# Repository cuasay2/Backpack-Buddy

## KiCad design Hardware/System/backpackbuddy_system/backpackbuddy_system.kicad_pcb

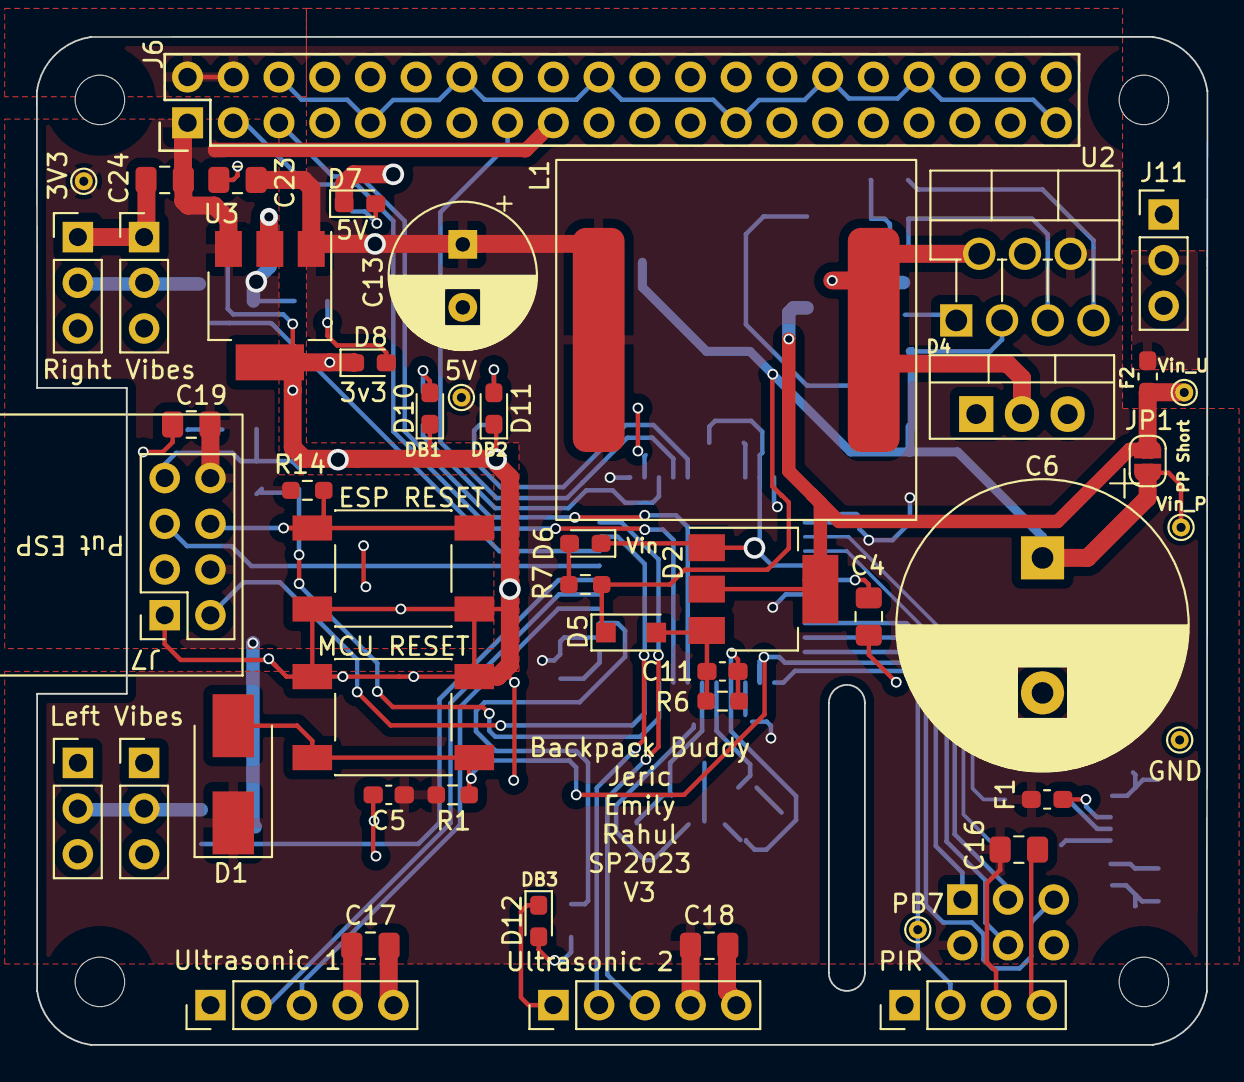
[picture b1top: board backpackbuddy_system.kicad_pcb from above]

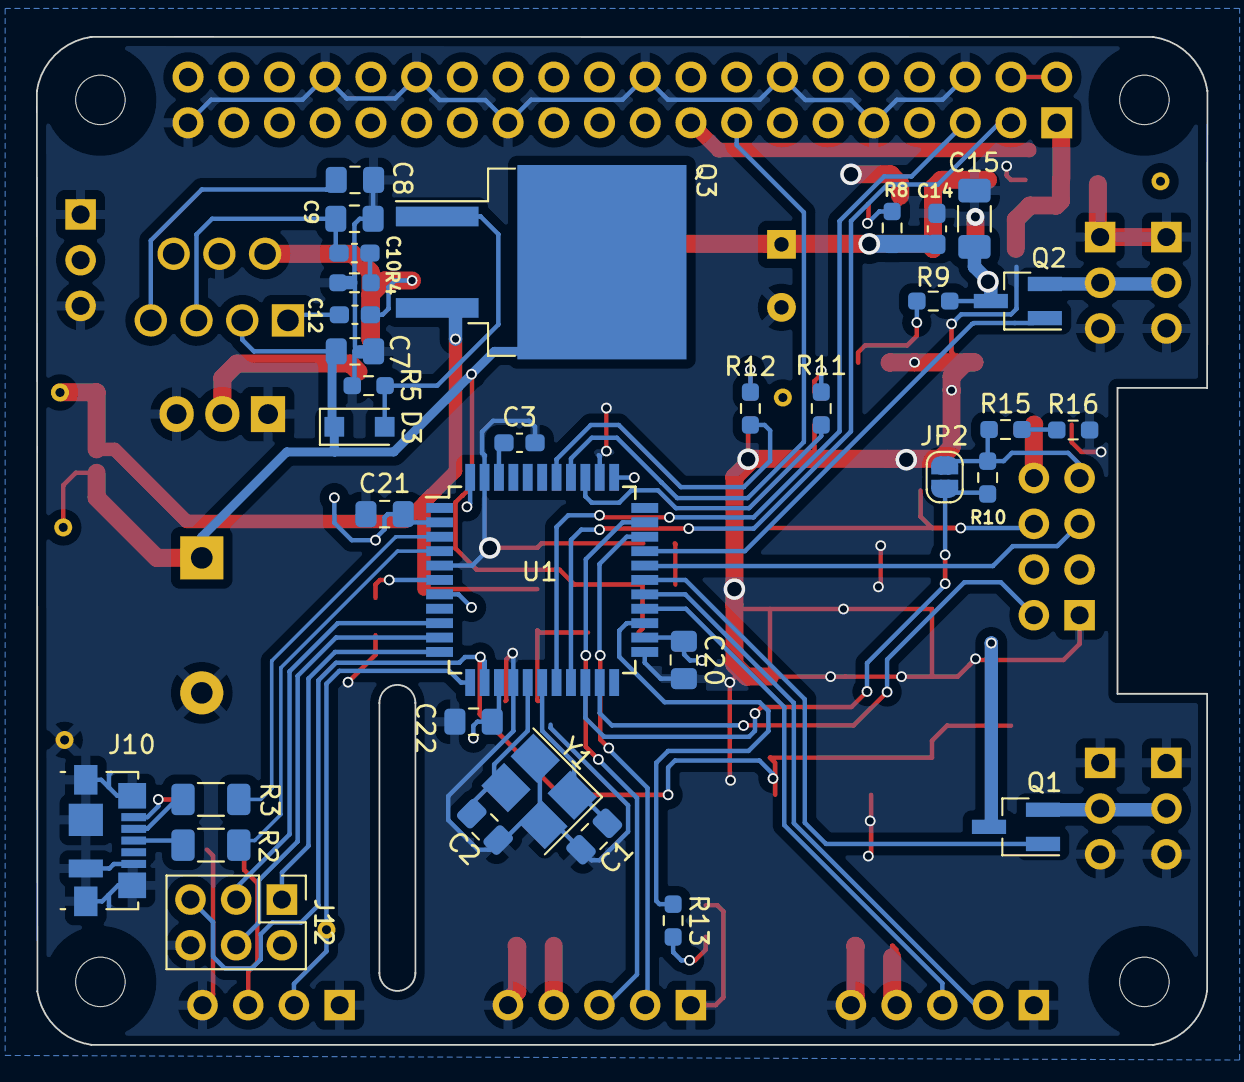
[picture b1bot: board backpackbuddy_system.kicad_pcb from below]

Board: 2 copper layers, 65.0 x 56.0 mm, 87 parts (34 on the bottom side), 53 nets.

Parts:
C1, C2: 22pF; C_0805_2012Metric_Pad1.18x1.45mm_HandSolder
C3, C5, C11: 0.1uF; C_0603_1608Metric_Pad1.08x0.95mm_HandSolder
C4: 1uF; C_0805_2012Metric_Pad1.18x1.45mm_HandSolder
C6: 2200uF; CP_Radial_D16.0mm_P7.50mm
C7: 4.7uF; C_0805_2012Metric_Pad1.18x1.45mm_HandSolder
C8, C16, C17, C18, C19, C20, C21, C22, C23, C24: 10uF; C_0805_2012Metric_Pad1.18x1.45mm_HandSolder
C9: 680pF; C_0805_2012Metric_Pad1.18x1.45mm_HandSolder
C10: 1200pF; C_0603_1608Metric_Pad1.08x0.95mm_HandSolder
C12: 0.22uF; C_0603_1608Metric_Pad1.08x0.95mm_HandSolder
C13: 470uF; CP_Radial_D8.0mm_P3.50mm
C14: 0.47uF; C_0603_1608Metric_Pad1.08x0.95mm_HandSolder
C15: 33uF; C_1206_3216Metric_Pad1.33x1.80mm_HandSolder
D1: 1V; D_SMB_Handsoldering
D2: S602TS; SOT-223-3_TabPin2
D3: 20V; D_SOD-123F
D4: FMW-2156; TO-220-3_Vertical
D5: 27V; D_SOD-123F
D6: Vin; LED_0603_1608Metric_Pad1.05x0.95mm_HandSolder
D7: 5V; LED_0603_1608Metric_Pad1.05x0.95mm_HandSolder
D8: 3v3; LED_0603_1608Metric_Pad1.05x0.95mm_HandSolder
D10: DB1; LED_0603_1608Metric_Pad1.05x0.95mm_HandSolder
D11: DB2; LED_0603_1608Metric_Pad1.05x0.95mm_HandSolder
D12: DB3; LED_0603_1608Metric_Pad1.05x0.95mm_HandSolder
F1: 500mA; Fuse_0603_1608Metric_Pad1.05x0.95mm_HandSolder
F2: 4A; Fuse_0603_1608Metric_Pad1.05x0.95mm_HandSolder
H1, H2, H3, H4: MountingHole; RPi_Hat_Mounting_Hole
J1: PIR; PinHeader_1x04_P2.54mm_Vertical
J2: Ultrasonic 2; PinHeader_1x05_P2.54mm_Vertical
J3: Ultrasonic 1; PinHeader_1x05_P2.54mm_Vertical
J4: Left Vibes; PinHeader_1x03_P2.54mm_Vertical
J5: Left Vibration 2; PinHeader_1x03_P2.54mm_Vertical
J6: RPi_GPIO; Pin_Header_Straight_2x20
J7: ESP8266
J8: Right Vibes; PinHeader_1x03_P2.54mm_Vertical
J9: Right Vibration 2; PinHeader_1x03_P2.54mm_Vertical
J10: USB_B_Micro; USB_Micro-B_Molex_47346-0001
J11: Battery; PinHeader_1x03_P2.54mm_Vertical
J12: ICSP; PinHeader_2x03_P2.54mm_Vertical
JP1, JP2: PP Short; SolderJumper-2_P1.3mm_Open_RoundedPad1.0x1.5mm
L1: 56uH; Inductor_IHLP6767GZER560M11
PB7: PIR; TestPoint_THTPad_D1.0mm_Drill0.5mm
Q1, Q2: Q_NMOS_GSD; SOT-23_Handsoldering
Q3: SIHF9Z24STRR-GE3; TO-263-2
R1, R7, R14: 10k; R_0603_1608Metric_Pad0.98x0.95mm_HandSolder
R2, R3: 22; R_1206_3216Metric_Pad1.30x1.75mm_HandSolder
R4: 39k; R_0603_1608Metric_Pad0.98x0.95mm_HandSolder
R5, R6, R8, R9, R10, R11, R12, R13, R15, R16: 1k; R_0603_1608Metric_Pad0.98x0.95mm_HandSolder
SW1: ESP RESET; RST_SW
SW2: MCU RESET; RST_SW
TP1: Vin_U; TestPoint_THTPad_D1.0mm_Drill0.5mm
TP2: GND; TestPoint_THTPad_D1.0mm_Drill0.5mm
TP3: Vin_P; TestPoint_THTPad_D1.0mm_Drill0.5mm
TP4: 5V; TestPoint_THTPad_D1.0mm_Drill0.5mm
TP5: 3V3; TestPoint_THTPad_D1.0mm_Drill0.5mm
U1: ATmega32U4-A; TQFP-44_10x10mm_P0.8mm
U2: SI-8050Y; TO-220F-7_P2.54x3.7mm_StaggerOdd_Lead3.5mm_Vertical
U3: LM3940; SOT-223
Y1: 16MHz; Crystal_SMD_3225-4Pin_3.2x2.5mm_HandSoldering

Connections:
+3V3: C15.1, C19.1, C24.1, J6.1, J6.17, J7.4, J7.8, Q1.3 (D), Q2.3 (D), R9.1, R14.1, TP5.1, U3.3 (Vout)
+5V: C5.1, C13.1, C14.1, C16.1, C17.1, C18.1, C20.1, C21.1, C22.1, C23.1, D1.1 (K), F1.2, J1.3, J2.4, J3.4, J6.2, J6.4, J12.2, L1.2, R1.1, R8.1, TP4.1, U1.2 (UVCC), U1.7 (VBUS), U1.14 (VCC), U1.24 (AVCC), U1.34 (VCC), U1.44 (AVCC), U2.6 (FB), U3.1 (Vin)
/ESP RESET: J7.6, R14.2, SW1.1
/ESP_RX: J7.7, JP2.1 (A), R10.2, R15.1
/MISO: J12.1, U1.11 (PB3)
/MOSI: J12.4, U1.10 (PB2)
/PD2/RX: JP2.2 (B), R10.1, U1.20 (PD2)
/Power/18V PROTECTED: C6.1, C7.1, D3.1 (K), D5.1 (K), JP1.2 (B), Q3.2 (D), R7.1, TP3.1, U2.3 (IN)
/RESET: D1.2 (A), J12.5, R1.2, SW2.1, U1.13 (~RESET)
/Raspberry Pi/GPIO2_SDA: J6.3, U1.19 (PD1)
/Raspberry Pi/GPIO3_SCL: J6.5, U1.18 (PD0)
/Raspberry Pi/GPIO22: J6.15, U1.37 (PF6)
/SCLK: J12.3, U1.9 (PB1)
/microcontroller/D+: R2.2, U1.4 (D+)
/microcontroller/D-: R3.2, U1.3 (D-)
/microcontroller/PB4: Q1.1 (G), U1.28 (PB4)
/microcontroller/PB5: J7.5, U1.29 (PB5)
/microcontroller/PB6: Q2.1 (G), U1.30 (PB6)
/microcontroller/PB7: J1.2, PB7.1, U1.12 (PB7)
/microcontroller/PC6: J2.2, U1.31 (PC6)
/microcontroller/PC7: J2.3, U1.32 (PC7)
/microcontroller/PD3/TX: J7.2, U1.21 (PD3)
/microcontroller/PD4: R13.1, U1.25 (PD4)
/microcontroller/PD6: J3.3, U1.26 (PD6)
/microcontroller/PD7: J3.2, U1.27 (PD7)
/microcontroller/PF5: R12.1, U1.38 (PF5)
/microcontroller/PF7: R11.1, U1.36 (PF7)
GND: C1.1, C2.1, C3.2, C4.2, C5.2, C6.2, C7.2, C8.2, C9.2, C11.2, C13.2, C14.2, C15.2, C16.2, C17.2, C18.2, C19.2, C20.2, C21.2, C22.2, C23.2, C24.2, D2.1 (K), D4.1 (A), D4.3 (A), D6.1 (K), D7.1 (K), D8.1 (K), D10.1 (K), D11.1 (K), D12.1 (K), J1.1, J1.4, J2.1, J2.5, J3.1, J3.5, J4.1, J4.3, J5.1, J5.3, J6.6, J6.9, J6.14, J6.20, J6.25, J6.30, J6.34, J6.39, J7.1, J8.1, J8.3, J9.1, J9.3, J10.5 (GND), J10.6 (Shield), J11.1, J11.3, J12.6, R4.2, R5.2, R6.2, R16.2, SW1.2, SW2.2, TP2.1, U1.5 (UGND), U1.15 (GND), U1.23 (GND), U1.35 (GND), U1.43 (GND), U2.4 (GND), U3.2 (GND), U3.4 (GND), Y1.2, Y1.4
unnamed: C1.2, U1.17 (XTAL1), Y1.1
unnamed: C2.2, U1.16 (XTAL2), Y1.3
unnamed: C3.1, U1.42 (AREF)
unnamed: C4.1, U1.6 (UCAP)
unnamed: C8.1, U2.7 (EN/SS)
unnamed: C9.1, C10.1, U2.5 (COMP)
unnamed: C10.2, R4.1
unnamed: C11.1, D2.3 (G), D5.2 (A), R6.1
unnamed: C12.1, U2.1 (BS)
unnamed: C12.2, D4.2 (K), L1.1, U2.2 (SW)
unnamed: D2.2 (A), F2.2, JP1.1 (A), Q3.3 (S), TP1.1
unnamed: D3.2 (A), Q3.1 (G), R5.1
unnamed: D6.2 (A), R7.2
unnamed: D7.2 (A), R8.2
unnamed: D8.2 (A), R9.2
unnamed: D10.2 (A), R11.2
unnamed: D11.2 (A), R12.2
unnamed: D12.2 (A), R13.2
unnamed: F1.1, J10.1 (VBUS)
unnamed: F2.1, J11.2
unnamed: J4.2, J5.2, Q1.2 (S)
unnamed: J8.2, J9.2, Q2.2 (S)
unnamed: J10.2 (D-), R3.1
unnamed: J10.3 (D+), R2.1
unnamed: R15.2, R16.1

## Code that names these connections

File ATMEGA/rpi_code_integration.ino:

#include <Wire.h>

#define SLAVE_ADDRESS 0x08

byte i2c_data_byte = 0;
const int trigPin = 12; //PD6
const int echoPin = 6; //PD7
const int trigPin2 = 13; //PC7
const int echoPin2 = 5; //PC6
const int heartbeat_LED = A0; //PF7
const int vibration_left = 8; //PB4
const int vibration_right = 10; //PB6

// defines variables
long duration;
long duration2;
int distance;
int distance2;
int heartbeat_counter;
int vibes_counter = 0; 
int temp = 0;
int heartbeatState = 0;
int emergency_data = 0;

void setup() 
{
  pinMode(trigPin, OUTPUT); // Sets the trigPin as an Output
  pinMode(echoPin, INPUT); // Sets the echoPin as an Input
  pinMode(trigPin2, OUTPUT); // Sets the trigPin as an Output
  pinMode(echoPin2, INPUT); // Sets the echoPin as an Input
  pinMode(heartbeat_LED, OUTPUT);
  pinMode(vibration_right, OUTPUT);
  Serial.begin(9600); // Starts the serial communication
  Wire.begin(SLAVE_ADDRESS);
  Wire.onReceive(receiveData);
  Wire.onRequest(sendData);
}

void loop() { 
  emergency_data = 0; //reset emergency stat

  //Heartbeat
  if(heartbeatState == 0){
    heartbeatState = 1;
  }
  else{
    heartbeatState = 0;
  }
  digitalWrite(heartbeat_LED, heartbeatState);

  //Ultrasonic Sensor with RPI
  digitalWrite(trigPin, LOW);
  delayMicroseconds(2);
  // Sets the trigPin on HIGH state for 10 micro seconds
  digitalWrite(trigPin, HIGH);
  delayMicroseconds(10);
  digitalWrite(trigPin, LOW);
  // Reads the echoPin, returns the sound wave travel time in microseconds
  duration = pulseIn(echoPin, HIGH);
  distance = duration * 0.034 / 2;

  //send emergency signal to rpi
  if(distance <= 35) {
    emergency_data = 1;
  }

  //Close up vibration
  if(distance <= 65) {
    if(i2c_data_byte == 10) {
        digitalWrite(vibration_left, 1);
        digitalWrite(vibration_right, 0);
      }
      else if(i2c_data_byte == 20) {
        digitalWrite(vibration_left, 1);
        digitalWrite(vibration_right, 1);
      }
      else if(i2c_data_byte == 30) {
        digitalWrite(vibration_left, 0);
        digitalWrite(vibration_right, 1);
      }
      else {
        digitalWrite(vibration_left, 1);
        digitalWrite(vibration_right, 1);
      }
    // digitalWrite(vibration_left, 1);
    // digitalWrite(vibration_right, 1);
  }
  //Far away vibration
  else {
    if((i2c_data_byte/10) > 0) {
      if(vibes_counter < 3) {
        if(i2c_data_byte == 10) {
          digitalWrite(vibration_left, 1);
          digitalWrite(vibration_right, 0);
        }
        else if(i2c_data_byte == 20) {
          digitalWrite(vibration_left, 1);
          digitalWrite(vibration_right, 1);
        }
        else {
          digitalWrite(vibration_left, 0);
          digitalWrite(vibration_right, 1);
        }
        vibes_counter++;
      }

      else if(vibes_counter >= 3 && vibes_counter < 80) {
        digitalWrite(vibration_left, 0);
        digitalWrite(vibration_right, 0);
        vibes_counter++;
      }
      else {
        digitalWrite(vibration_left, 0);
        digitalWrite(vibration_right, 0);
        vibes_counter = 0;
      }
    }
    else {
      digitalWrite(vibration_left, 0);
      digitalWrite(vibration_right, 0);
      vibes_counter = 0;
    }
    
  }
  
  //VIBRATION STATE DECLARATIONS
  //    0 - no vibrations at all
  //   10 - vibrate left if person detected in camera
  //   20 - vibrate both if person detected in camera
  //   30 - vibrate right if person detected in camera
  
  delay(100);


  
}

void receiveData(int bytecount)
{
  for (int i = 0; i < bytecount; i++) {
    i2c_data_byte = Wire.read();
  }
  // Serial.println(i2c_data_byte);
}

void sendData()
{
  Wire.write(emergency_data);
}

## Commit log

2023-02-19 first kicad test schematic
2023-02-19 started 12 to 5V sch
2023-02-19 progress on power circuit
2023-02-20 created mcu symbol
2023-02-20 added LED indicators
2023-02-24 fixed all library issues and ERC errors
2023-02-25 fixed C6 and F1, chose L1 part and created footprint for it
2023-02-25 microcontroller
2023-02-27 more changes
2023-02-27 vibration stuff
2023-02-27 added safe connectors
2023-02-28 labels and stuff almost done
2023-02-28 combining both sheets
2023-02-28 more integration changes
2023-02-28 updated fields
2023-02-28 schematic mostly done, just need to fix ERC, decoup caps, TP
2023-03-02 random other sch changes
2023-03-02 fixed an error
2023-03-02 fixed layout errors
2023-03-02 added ESP8266 footprint, more testpoints, mounting holes
2023-03-02 modified esp8266 footprint
2023-03-05 fixed L1 footprint
2023-03-05 fixed lm3940 symbol, changed crystal stuff
2023-03-05 fixed table values
2023-03-05 changed LED resistor value
2023-03-05 changed D1, the MCU reset switch diode from 50V to 1V, changed crystal caps to 22pF
2023-03-05 pp: flipped Q3 pins, changed values for D3 and D5 and updated datasheets; also fixed solder jump short pp such that its fused
2023-03-05 adding the raspberry pi io-shield template files
2023-03-06 pi hat stuff nothing to do with our design
2023-03-06 about to go crazy with the raspberry pi setup on schematic then will layout after dinner hehe
2023-03-06 pin matched everything
2023-03-06 pull down resistor to ESP reset
2023-03-06 decoupling caps
2023-03-06 board outline redo
2023-03-06 components placed time to wire
2023-03-06 almost done
2023-03-06 first draft done :))) still errors but thats because i was too lazy to do no connects as of rn
2023-03-07 silkscreen done
2023-03-07 minor thingies
2023-03-07 pushing
2023-03-07 gerbers
2023-03-07 updated silkscreen
2023-03-15 added directories for arduino and rpi code
2023-03-17 fixed reset state with LEDs
2023-03-21 Board run 2 start -> rewire arduino connections
2023-03-21 pcb redone
2023-03-26 updated thing
2023-03-31 right/left detection working
2023-04-05 version 3 board
2023-04-05 version 3 fixed some silkscreen
2023-04-05 pp short
2023-04-16 Add files via upload
    need to put it in a folder named ESP8266Backpackbuddy
2023-04-24 backup plan arduino code
